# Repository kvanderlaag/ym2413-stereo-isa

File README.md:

# OPLL Stereo ISA Sound Card

## What is this?

It's an ISA sound card that uses two YM2413s (otherwise known as the OPLL) in stereo to make noise.

## Okay, but why?

I don't know, you tell me. You're the one looking at this repository.

## What can I do with it?

Whatever you want, I'm not your dad.

## Okay, but I mean, what software can I run with it?

If you're asking what software supports it, the answer is "none."

## Then I ask again: why?

Because there weren't enough weird sound cards for the PC, apparently.

## How do I program it?

The jumper block lets you select a base address from 210h, 220h, 230h, 240h, 250h, or 260h. Assuming you have the base address set at 210h, the left channel OPLL lives on 210h-201h, and the right channel OPLL lives on 212h-213h. Write to the first address for a chip to select a register in the OPLL, and write to the second address to write data to that register.

That's it. That's the card.

## Okay, but how do I program the OPLL?

I actually have no idea. You'll want to refer to the datasheet, which is in this repository as "YM2413 Datasheet.pdf". Pages 4 and 5 contain the register map, and register data. In short, the OPLL is a cut-rate OPL that was originally intended for cheap-ass pachinko machines and other things that make annoying noises at you to get your attention. I think it also does Teletext, if that floats your boat for some reason. It supports up to nine voices, but only one of them is user-programmable. The rest you get to choose from a bunch of patches that live in ROM. Please let me know if you write anything interesting for this. I sure haven't yet.

## What if I just want to build one?

Now it's my turn to ask: why? Either way, OPLL-Stereo.zip is in the "gerbil" folder; you should be able to fire that off to JLCPCB and select "choose location" for the order number; the gerbers are all set up for that. The BOM is in a CSV file here with DigiKey links to the parts the board was designed for. If you find a 10K audio taper pot that fits that footprint, please let me know; I'm using a 50K with a 15K fixed resistor in parallel right now and it kind of sucks. Everything is pretty basic as far as parts go; a couple of the logic chips have been in shortage, but you should be able to substitute HCTs for the LSes if you need to, and everything should be actively available. The bracket is a Keystone 9202, and screws are listed. You'll need to drill a hole for the audio jack (I've been using a 9/32" bit) and cut a slot for a volume wheel, if you want to add one. There's a 3D-printable volume knob and card bracket in the `Mechanical` folder if you want to go that route. The volume knob attaches with an M1.4x0.3 5mm machine screw.

## I built one and it doesn't work! What the hell, man?

I'm not surprised.

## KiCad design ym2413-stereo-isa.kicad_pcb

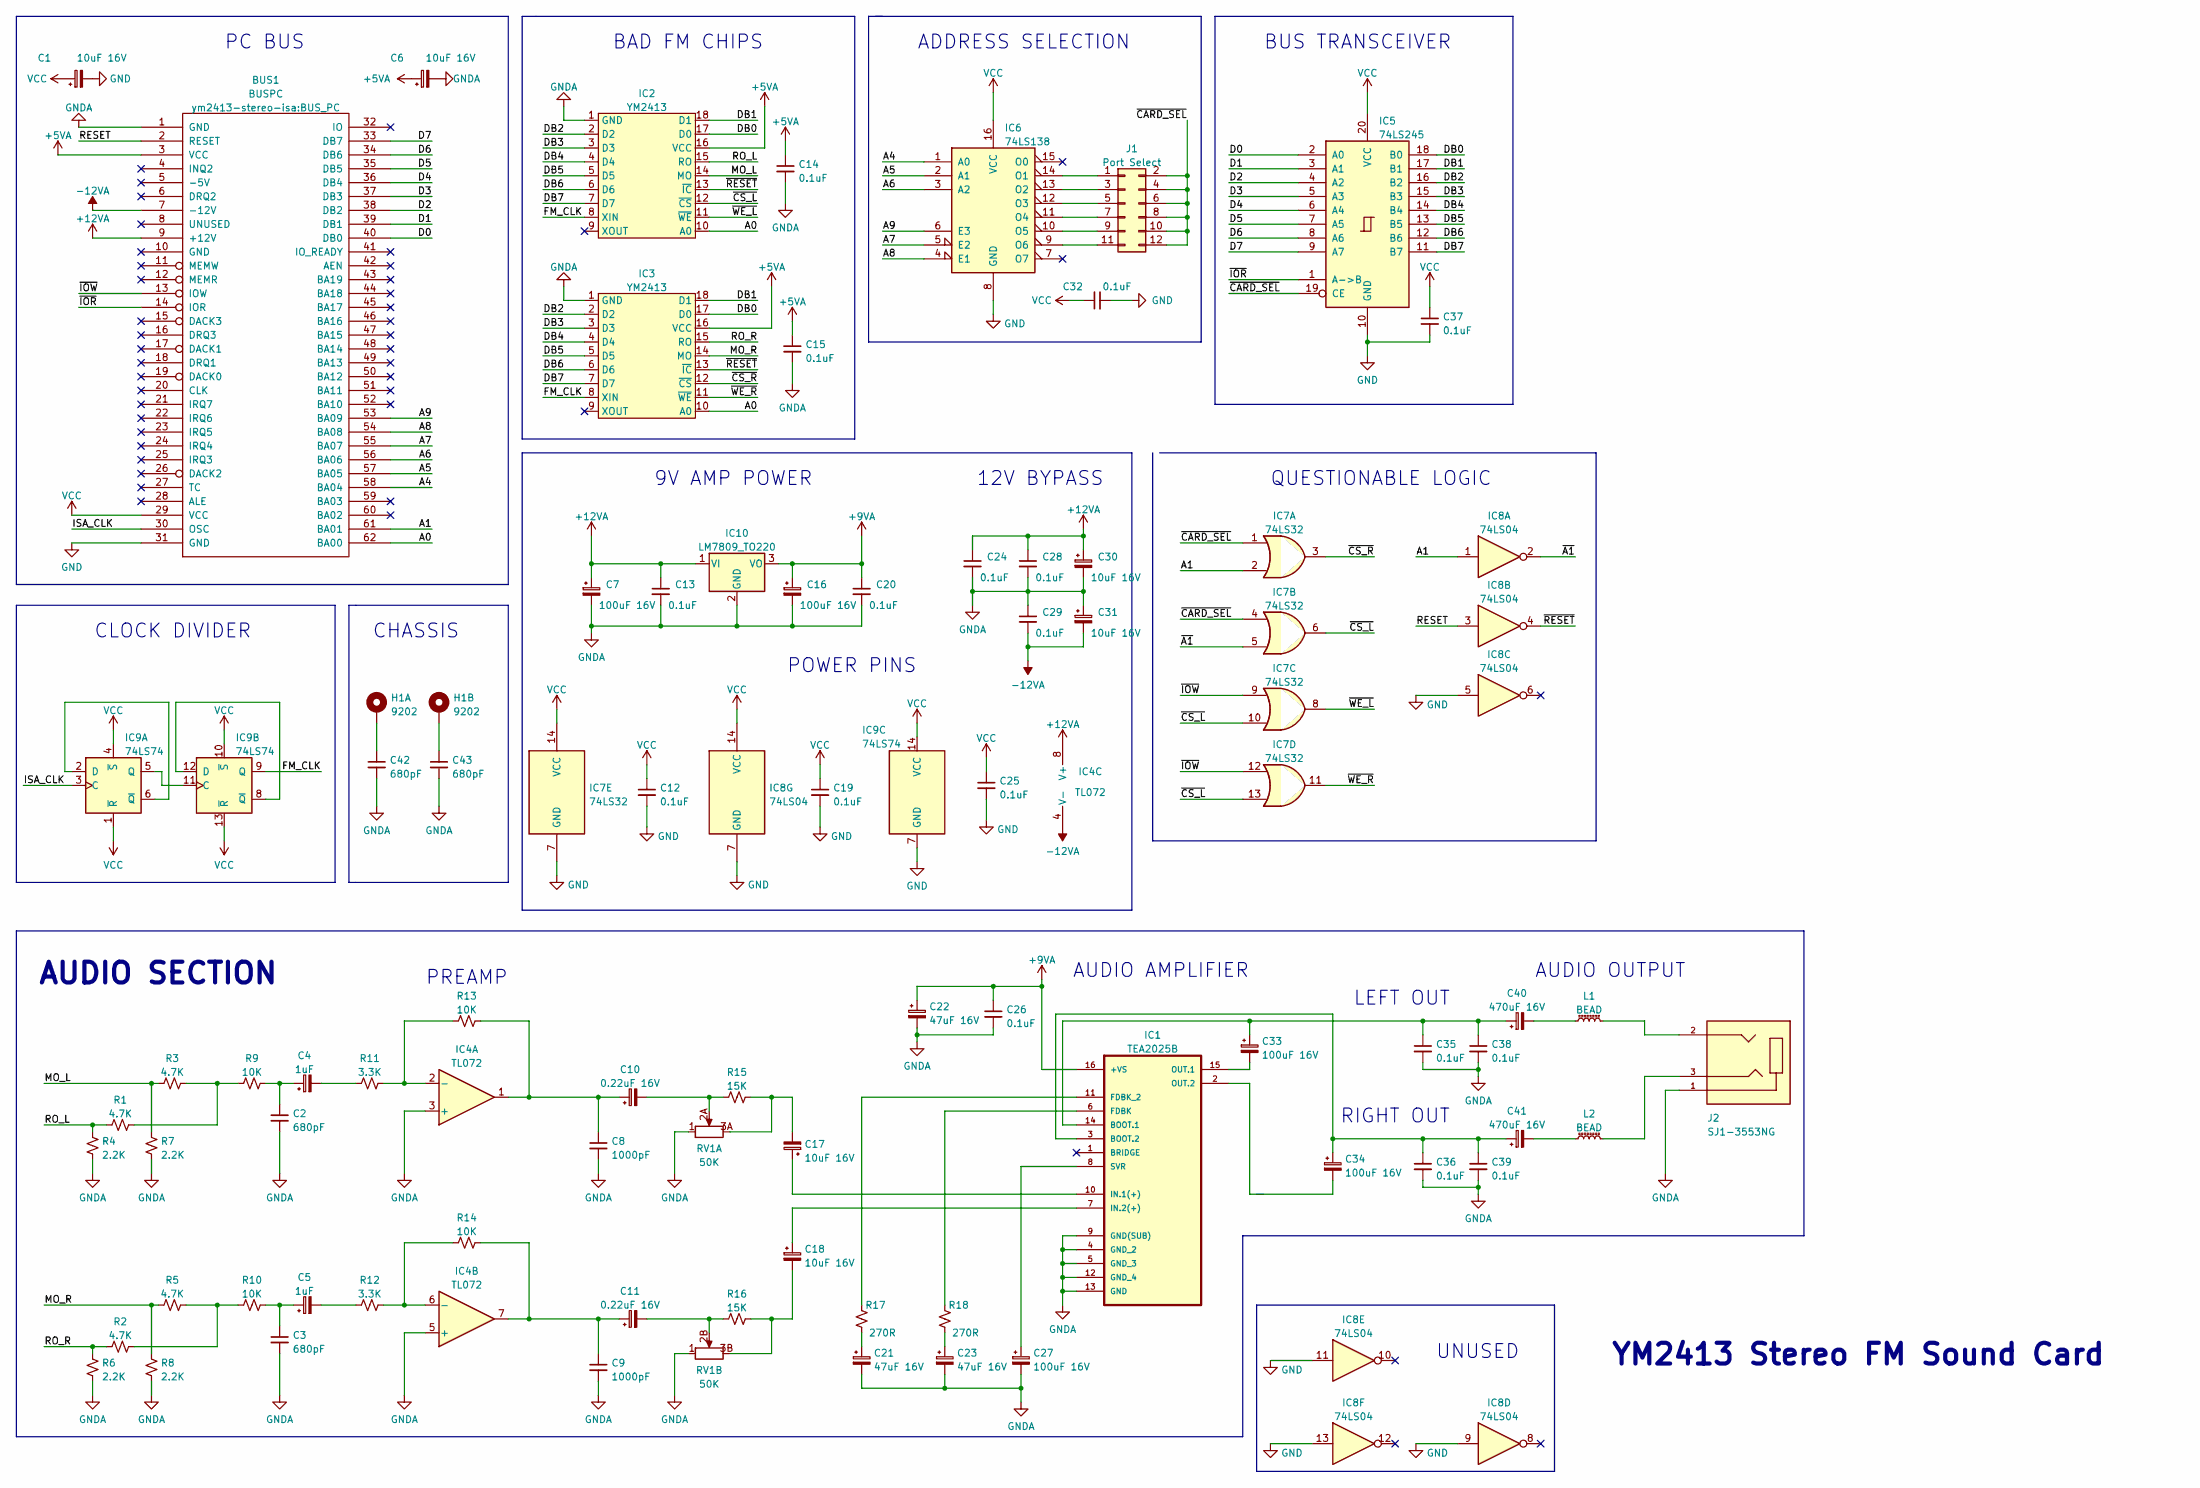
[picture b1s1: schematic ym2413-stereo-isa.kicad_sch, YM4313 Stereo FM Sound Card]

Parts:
BUS1: BUSPC; BUS_PC
C1, C6, C17, C18, C30, C31: 10uF 16V; CP_Radial_D5.0mm_P2.50mm
C2, C3, C42, C43: 680pF; C_Disc_D4.7mm_W2.5mm_P5.00mm
C4, C5: 1uF; CP_Radial_D6.3mm_P2.50mm
C7, C16, C27, C33, C34: 100uF 16V; CP_Radial_D5.0mm_P2.50mm
C8, C9: 1000pF; C_Disc_D4.7mm_W2.5mm_P5.00mm
C10, C11: 0.22uF 16V; CP_Radial_D5.0mm_P2.50mm
C12, C13, C14, C15, C19, C20, C24, C25, C26, C28, C29, C32, C35, C36, C37, C38, C39: 0.1uF; C_Disc_D5.1mm_W3.2mm_P5.00mm
C21, C22, C23: 47uF 16V; CP_Radial_D5.0mm_P2.50mm
C40, C41: 470uF 16V; CP_Radial_D8.0mm_P3.50mm
H1: 9202; MNT_KEYSTONE_9202
IC1: TEA2025B; DIP-16_W7.62mm; MPN TEA2025B
IC2, IC3: YM2413; DIP-18_W7.62mm_Socket
IC4: TL072; DIP-8_W7.62mm
IC5: 74LS245; DIP-20_W7.62mm
IC6: 74LS138; DIP-16_W7.62mm
IC7: 74LS32; DIP-14_W7.62mm
IC8: 74LS04; DIP-14_W7.62mm
IC9: 74LS74; DIP-14_W7.62mm
IC10: LM7809_TO220; TO-220-3_Horizontal_TabDown
J1: Port Select; PinHeader_2x06_P2.54mm_Vertical
J2: SJ1-3553NG; CUI_SJ1-3553NG
L1, L2: BEAD; L_Axial_L7.0mm_D3.3mm_P10.16mm_Horizontal_Fastron_MICC
R1, R2, R3, R5: 4.7K; R_Axial_DIN0204_L3.6mm_D1.6mm_P5.08mm_Horizontal
R4, R6, R7, R8: 2.2K; R_Axial_DIN0204_L3.6mm_D1.6mm_P5.08mm_Horizontal
R9, R10, R13, R14: 10K; R_Axial_DIN0204_L3.6mm_D1.6mm_P5.08mm_Horizontal
R11, R12: 3.3K; R_Axial_DIN0204_L3.6mm_D1.6mm_P5.08mm_Horizontal
R15, R16: 15K; R_Axial_DIN0204_L3.6mm_D1.6mm_P5.08mm_Horizontal
R17, R18: 270R; R_Axial_DIN0204_L3.6mm_D1.6mm_P5.08mm_Horizontal
RV1: 50K; GB_BOURNS_PDB08-DUAL

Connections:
+5VA: BUS1.3 (VCC), C6.1, C14.1, C15.1, IC2.16 (VCC), IC3.16 (VCC)
+9VA: C16.1, C20.1, C22.1, C26.1, IC1.16 (+VS), IC10.3 (VO)
+12VA: BUS1.9 (+12V), C7.1, C13.1, C24.1, C28.1, C30.1, IC4.8 (V+), IC10.1 (VI)
-12VA: BUS1.7 (-12V), C29.2, C31.2, IC4.4 (V-)
/A0: BUS1.62 (BA00), IC2.10 (A0), IC3.10 (A0)
/A1: BUS1.61 (BA01), IC7.2, IC8.1
/A4: BUS1.58 (BA04), IC6.1 (A0)
/A5: BUS1.57 (BA05), IC6.2 (A1)
/A6: BUS1.56 (BA06), IC6.3 (A2)
/A7: BUS1.55 (BA07), IC6.5 (E2)
/A8: BUS1.54 (BA08), IC6.4 (E1)
/A9: BUS1.53 (BA09), IC6.6 (E3)
/D0: BUS1.40 (DB0), IC5.2 (A0)
/D1: BUS1.39 (DB1), IC5.3 (A1)
/D2: BUS1.38 (DB2), IC5.4 (A2)
/D3: BUS1.37 (DB3), IC5.5 (A3)
/D4: BUS1.36 (DB4), IC5.6 (A4)
/D5: BUS1.35 (DB5), IC5.7 (A5)
/D6: BUS1.34 (DB6), IC5.8 (A6)
/D7: BUS1.33 (DB7), IC5.9 (A7)
/DB0: IC2.17 (D0), IC3.17 (D0), IC5.18 (B0)
/DB1: IC2.18 (D1), IC3.18 (D1), IC5.17 (B1)
/DB2: IC2.2 (D2), IC3.2 (D2), IC5.16 (B2)
/DB3: IC2.3 (D3), IC3.3 (D3), IC5.15 (B3)
/DB4: IC2.4 (D4), IC3.4 (D4), IC5.14 (B4)
/DB5: IC2.5 (D5), IC3.5 (D5), IC5.13 (B5)
/DB6: IC2.6 (D6), IC3.6 (D6), IC5.12 (B6)
/DB7: IC2.7 (D7), IC3.7 (D7), IC5.11 (B7)
/FM_CLK: IC2.8 (XIN), IC3.8 (XIN), IC9.9 (Q)
/ISA_CLK: BUS1.30 (OSC), IC9.3 (C)
/MO_L: IC2.14 (MO), R3.2, R7.1
/MO_R: IC3.14 (MO), R5.2, R8.1
/RESET: BUS1.2 (RESET), IC8.3
/RO_L: IC2.15 (RO), R1.2, R4.1
/RO_R: IC3.15 (RO), R2.2, R6.1
/~A1: IC7.5, IC8.2
/~CARD_SEL: IC5.19 (CE), IC7.1, IC7.4, J1.2, J1.4, J1.6, J1.8, J1.10, J1.12
/~CS_L: IC2.12 (~CS), IC7.6, IC7.10, IC7.13
/~CS_R: IC3.12 (~CS), IC7.3
/~IOR: BUS1.14 (IOR), IC5.1 (A->B)
/~IOW: BUS1.13 (IOW), IC7.9, IC7.12
/~RESET: IC2.13 (~IC), IC3.13 (~IC), IC8.4
/~WE_L: IC2.11 (~WE), IC7.8
/~WE_R: IC3.11 (~WE), IC7.11
GND: BUS1.31 (GND), C1.2, C12.2, C19.2, C25.2, C32.2, C37.2, IC5.10 (GND), IC6.8 (GND), IC7.7 (GND), IC8.5, IC8.7 (GND), IC8.9, IC8.11, IC8.13, IC9.7 (GND)
GNDA: BUS1.1 (GND), C2.2, C3.2, C6.2, C7.2, C8.2, C9.2, C13.2, C14.2, C15.2, C16.2, C20.2, C21.2, C22.2, C23.2, C24.2, C26.2, C27.2, C28.2, C29.1, C30.2, C31.1, C35.2, C36.2, C38.2, C39.2, C42.2, C43.2, IC1.4 (GND_2), IC1.5 (GND_3), IC1.9 (GND(SUB)), IC1.12 (GND_4), IC1.13 (GND), IC2.1 (GND), IC3.1 (GND), IC4.3 (+), IC4.5 (+), IC10.2 (GND), J2.1, R4.2, R6.2, R7.2, R8.2, RV1.1
unnamed: C2.1, C4.1, R9.1
unnamed: C3.1, C5.1, R10.1
unnamed: C4.2, R11.2
unnamed: C5.2, R12.2
unnamed: C8.1, C10.1, IC4.1, R13.1
unnamed: C10.2, R15.2, RV1.2A
unnamed: C9.1, C11.1, IC4.7, R14.1
unnamed: C11.2, R16.2, RV1.2B
unnamed: C17.1, IC1.10 (IN.1(+))
unnamed: C17.2, R15.1, RV1.3A
unnamed: C18.1, IC1.7 (IN.2(+))
unnamed: C18.2, R16.1, RV1.3B
unnamed: C21.1, R17.2
unnamed: C23.1, R18.2
unnamed: C27.1, IC1.8 (SVR)
unnamed: C33.1, C35.1, C38.1, C40.1, IC1.14 (BOOT.1)
unnamed: C33.2, IC1.15 (OUT.1)
unnamed: C34.1, C36.1, C39.1, C41.1, IC1.3 (BOOT.2)
unnamed: C34.2, IC1.2 (OUT.2)
unnamed: C40.2, L1.1
unnamed: C41.2, L2.1
unnamed: C42.1, H1.1
unnamed: C43.1, H1.2
unnamed: IC1.6 (FDBK), R18.1
unnamed: IC1.11 (FDBK_2), R17.1
unnamed: IC4.2 (-), R11.1, R13.2
unnamed: IC4.6 (-), R12.1, R14.2
unnamed: IC6.9 (O6), J1.11
unnamed: IC6.10 (O5), J1.9
unnamed: IC6.11 (O4), J1.7
unnamed: IC6.12 (O3), J1.5
unnamed: IC6.13 (O2), J1.3
unnamed: IC6.14 (O1), J1.1
unnamed: IC9.2 (D), IC9.6 (~Q)
unnamed: IC9.5 (Q), IC9.11 (C)
unnamed: IC9.8 (~Q), IC9.12 (D)
unnamed: J2.2, L1.2
unnamed: J2.3, L2.2
unnamed: R1.1, R3.1, R9.2
unnamed: R2.1, R5.1, R10.2
VCC: BUS1.29 (VCC), C1.1, C12.1, C19.1, C25.1, C32.1, C37.1, IC5.20 (VCC), IC6.16 (VCC), IC7.14 (VCC), IC8.14 (VCC), IC9.1 (~R), IC9.4 (~S), IC9.10 (~S), IC9.13 (~R), IC9.14 (VCC)

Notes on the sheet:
CHASSIS
POWER PINS
LEFT OUT
PREAMP
BUS TRANSCEIVER
CLOCK DIVIDER
AUDIO AMPLIFIER
AUDIO SECTION
RIGHT OUT
12V BYPASS
PC BUS
9V AMP POWER
BAD FM CHIPS
ADDRESS SELECTION
YM2413 Stereo FM Sound Card
AUDIO OUTPUT
QUESTIONABLE LOGIC
UNUSED

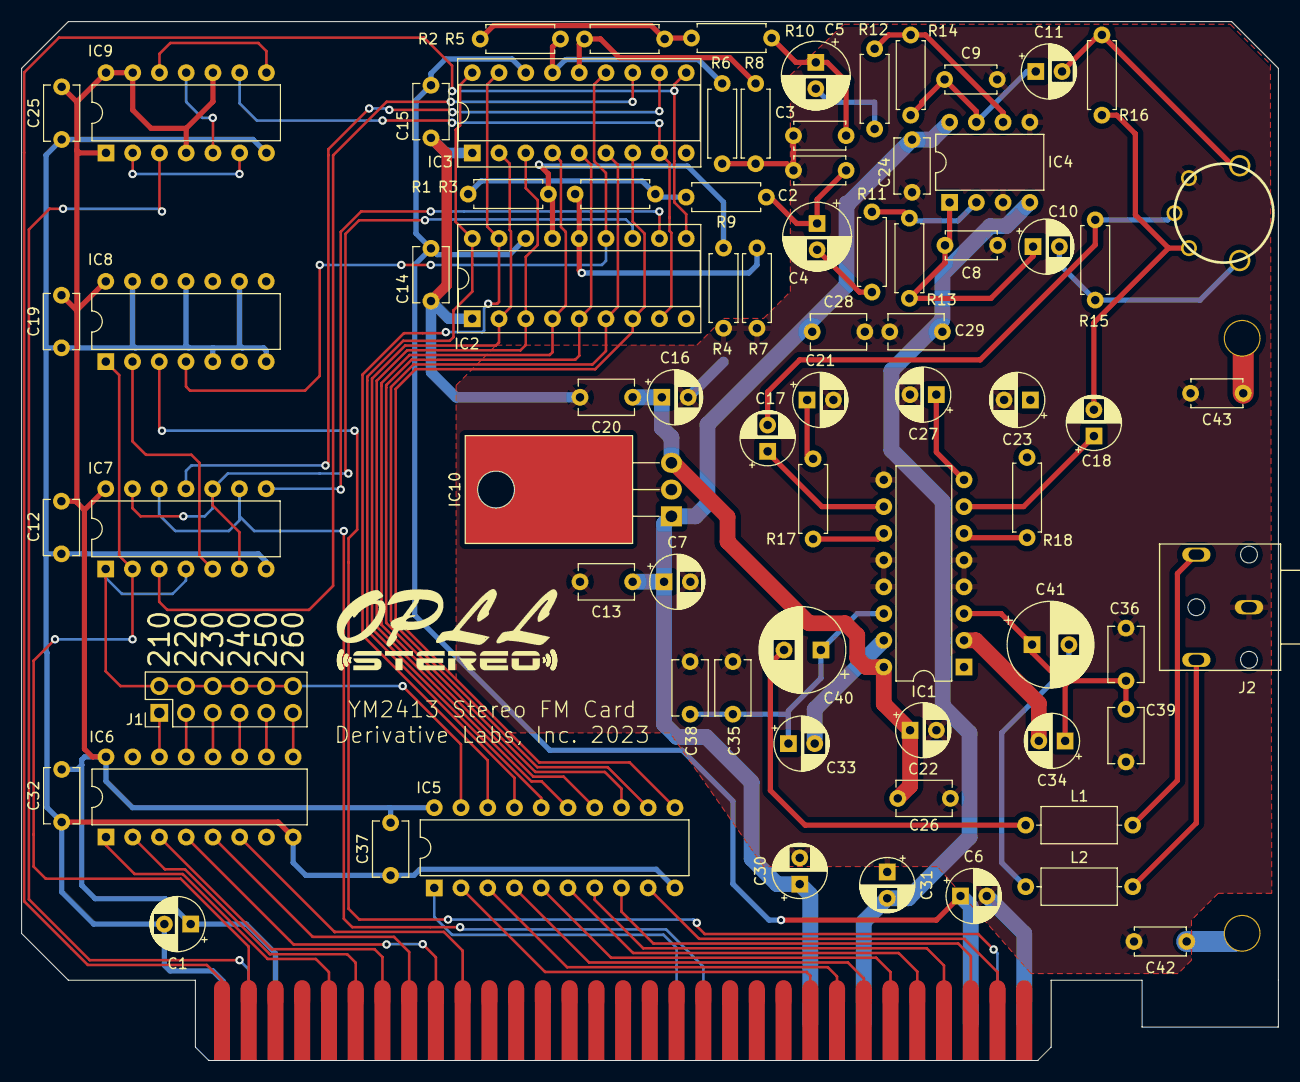
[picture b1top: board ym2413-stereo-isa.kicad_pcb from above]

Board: 2 copper layers, 119.4 x 98.7 mm, 78 parts (0 on the bottom side), 87 nets.

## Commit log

2023-03-04 Board Rev. 0
2023-03-04 update image; add datasheet
2023-03-08 Relocate volume pot and output jack; update gerbers; add CAD models
2023-03-08 fix X offset of bracket model
2023-03-29 correct capacitor footprint; move voltage divider; flip coupling caps
